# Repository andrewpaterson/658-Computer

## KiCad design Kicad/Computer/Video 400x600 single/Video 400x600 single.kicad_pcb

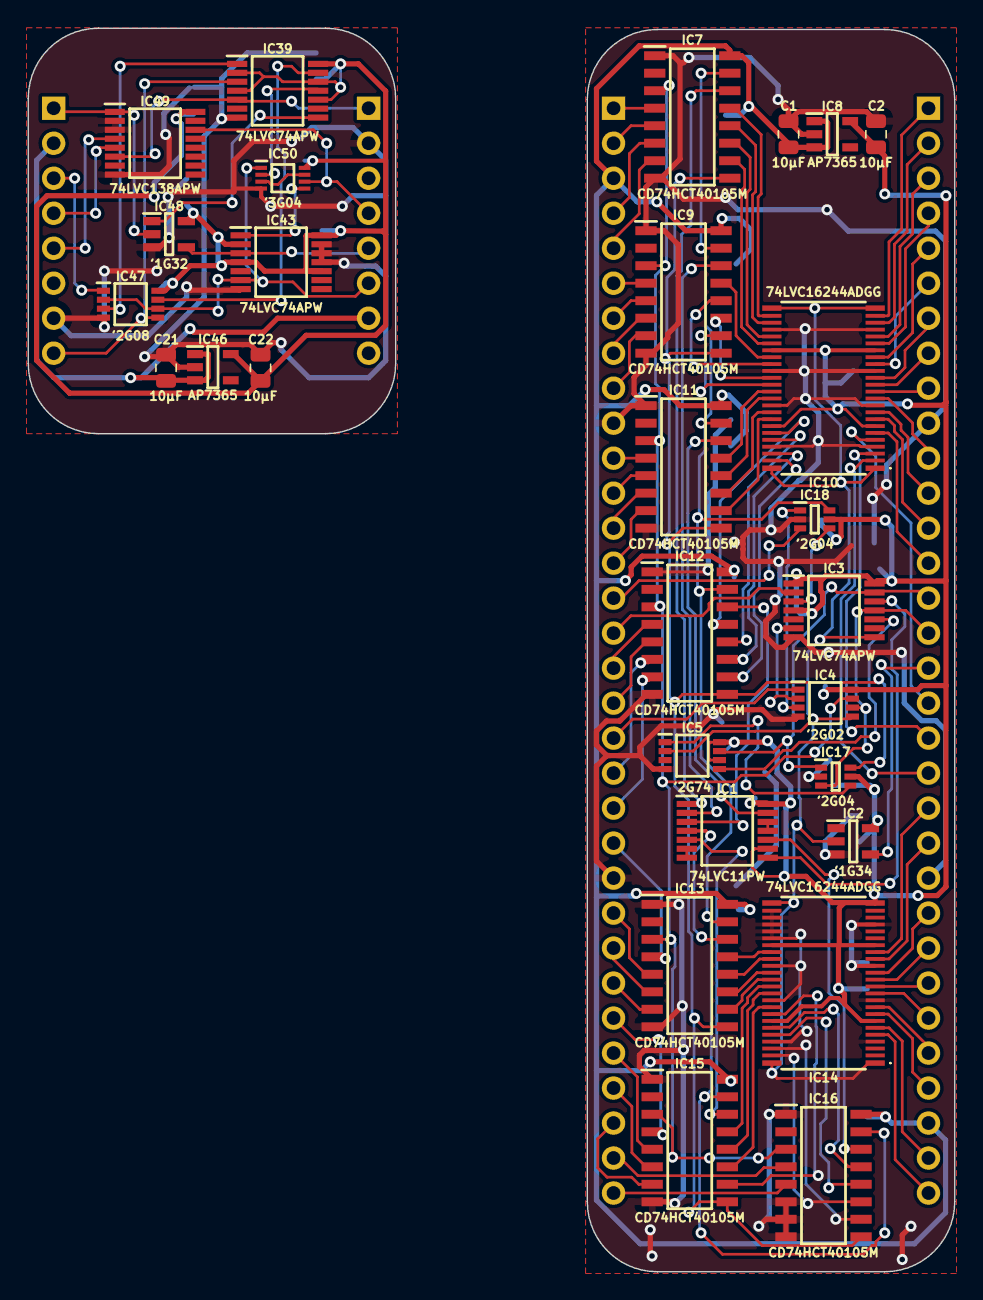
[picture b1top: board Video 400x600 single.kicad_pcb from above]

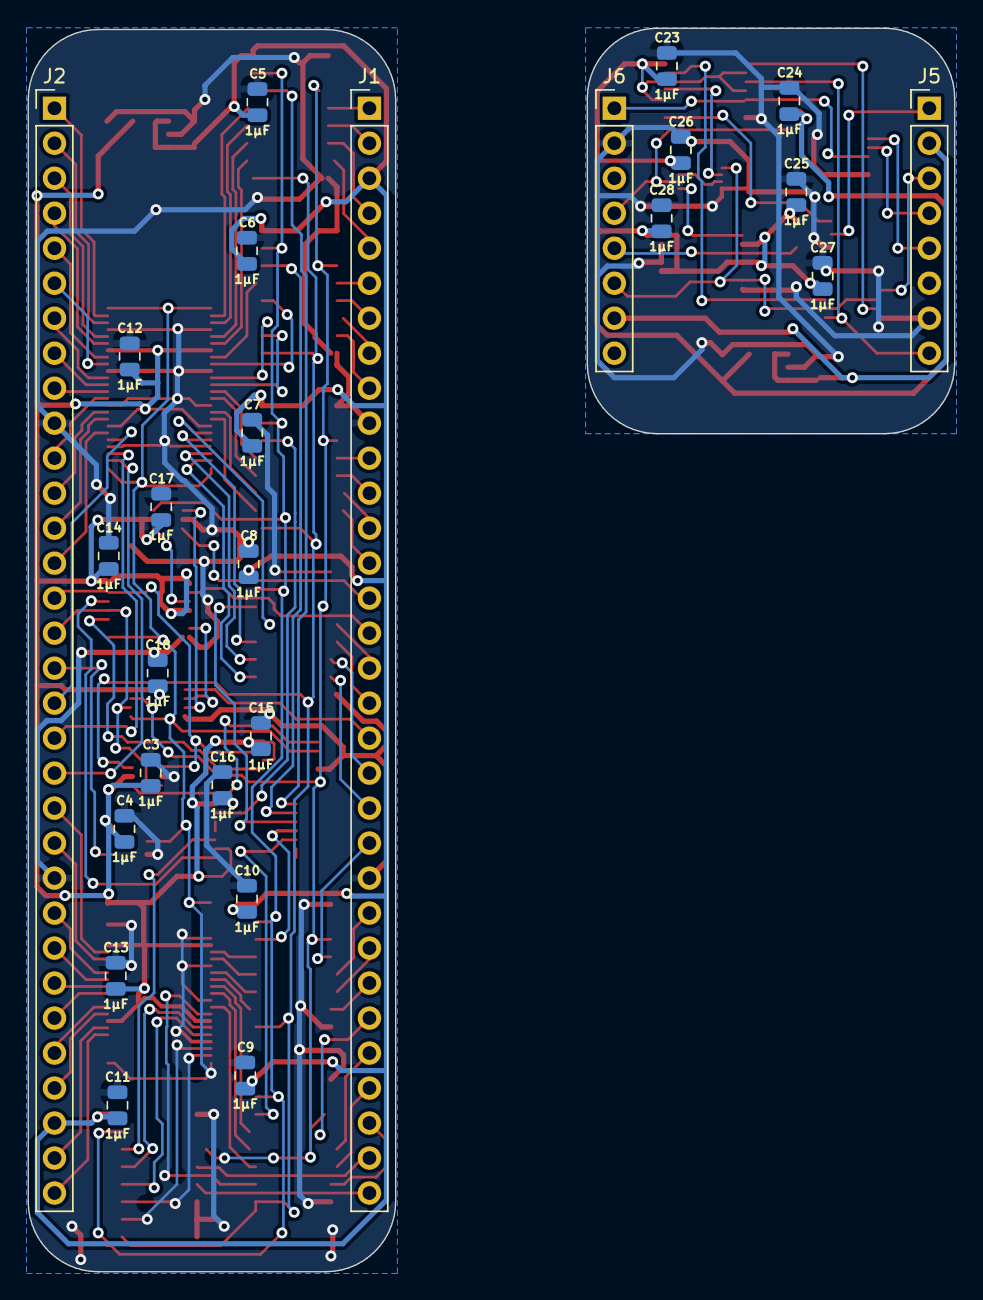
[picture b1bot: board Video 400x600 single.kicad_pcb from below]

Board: 2 copper layers, 67.2 x 90.3 mm, 54 parts (26 on the bottom side), 126 nets.

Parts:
C1, C2, C21, C22: 10µF; C_0805
C3, C4, C5, C6, C7, C8, C9, C10, C11, C12, C13, C14, C15, C16, C17, C18, C23, C24, C25, C26, C27, C28: 1μF; C_0805
IC1: 74LVC11PW,112; SOP65P640X110-14N
IC2: 74LVC1G34GV,125; SOT95P275X110-5N
IC3, IC39, IC43: 74LVC74APW,118; SOP65P640X110-14N
IC4: 74LVC2G02DP,125; SOP65P400X110-8N
IC5: 74LVC2G74DP,125; SOP65P400X110-8N
IC7, IC9, IC11, IC12, IC13, IC15, IC16: CD74HCT40105M; SOIC127P600X175-16N
IC8, IC46: AP7365-33WG-7; SOT95P285X130-5N
IC10, IC14: 74LVC16244ADGG,112; 74LVC16244ADGG112
IC17, IC18: 74LVC2G04GW-Q100H; SOP65P210X110-6N
IC47: 74LVC2G08DP-Q100H; SOP65P400X110-8N
IC48: 74LVC1G32GV,125; SOT95P275X110-5N
IC49: 74LVC138APW-Q100J; SOP65P640X110-16N
IC50: SN74LVC3G04DCUR; SOP50P310X90-8N
J1, J2: Conn_01x32_Pin; PinHeader_1x32_P2.54mm_Vertical
J5, J6: Conn_01x08_Pin; PinHeader_1x08_P2.54mm_Vertical

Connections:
/Asynchronous Write (FIFO)/3.3V: C2.1, C3.1, C4.1, C12.1, C13.1, C14.1, C15.1, C16.1, C17.1, C18.1, IC1.9 (3A), IC1.14 (3V), IC2.5 (3V), IC3.1 (~1RD), IC3.4 (~1SD), IC3.14 (3V), IC4.8 (3V), IC5.6 (~RD), IC5.8 (3V), IC8.5 (VOUT), IC10.7 (3V), IC10.18 (3V), IC10.31 (3V), IC10.42 (3V), IC14.7 (3V), IC14.18 (3V), IC14.24 (4~OE), IC14.31 (3V), IC14.42 (3V), IC17.5 (3V), IC18.5 (3V)
/Asynchronous Write (FIFO)/5V: C1.1, C5.1, C6.1, C7.1, C8.1, C9.1, C10.1, C11.1, IC7.16 (5V), IC8.1 (VIN), IC8.3 (EN), IC9.16 (5V), IC11.16 (5V), IC12.16 (5V), IC13.16 (5V), IC15.16 (5V), IC16.16 (5V), J1.3, J2.30
/Asynchronous Write (FIFO)/A0: IC11.4 (D0), J1.11
/Asynchronous Write (FIFO)/A1: IC11.5 (D1), J1.12
/Asynchronous Write (FIFO)/A2: IC11.6 (D2), J1.13
/Asynchronous Write (FIFO)/A3: IC11.7 (D3), J1.14
/Asynchronous Write (FIFO)/A4: IC12.4 (D0), J1.17
/Asynchronous Write (FIFO)/A5: IC12.5 (D1), J1.18
/Asynchronous Write (FIFO)/A6: IC12.6 (D2), J1.20
/Asynchronous Write (FIFO)/A7: IC12.7 (D3), J1.21
/Asynchronous Write (FIFO)/A8: IC13.4 (D0), J1.22
/Asynchronous Write (FIFO)/A9: IC13.5 (D1), J1.24
/Asynchronous Write (FIFO)/A10: IC13.6 (D2), J1.25
/Asynchronous Write (FIFO)/A11: IC13.7 (D3), J1.26
/Asynchronous Write (FIFO)/A12: IC15.4 (D0), J1.27
/Asynchronous Write (FIFO)/A13: IC15.5 (D1), J1.28
/Asynchronous Write (FIFO)/A14: IC15.6 (D2), J1.29
/Asynchronous Write (FIFO)/A15: IC15.7 (D3), J1.30
/Asynchronous Write (FIFO)/A16: IC16.4 (D0), J1.31
/Asynchronous Write (FIFO)/A17: IC16.5 (D1), J1.32
/Asynchronous Write (FIFO)/A_{OUT}0: IC10.37 (2A3), IC11.13 (Q0)
/Asynchronous Write (FIFO)/A_{OUT}1: IC10.38 (2A2), IC11.12 (Q1)
/Asynchronous Write (FIFO)/A_{OUT}2: IC10.40 (2A1), IC11.11 (Q2)
/Asynchronous Write (FIFO)/A_{OUT}3: IC10.41 (2A0), IC11.10 (Q3)
/Asynchronous Write (FIFO)/A_{OUT}4: IC10.43 (1A3), IC12.13 (Q0)
/Asynchronous Write (FIFO)/A_{OUT}5: IC10.44 (1A2), IC12.12 (Q1)
/Asynchronous Write (FIFO)/A_{OUT}6: IC10.46 (1A1), IC12.11 (Q2)
/Asynchronous Write (FIFO)/A_{OUT}7: IC10.47 (1A0), IC12.10 (Q3)
/Asynchronous Write (FIFO)/A_{OUT}8: IC13.13 (Q0), IC14.32 (3A3)
/Asynchronous Write (FIFO)/A_{OUT}9: IC13.12 (Q1), IC14.33 (3A2)
/Asynchronous Write (FIFO)/A_{OUT}10: IC13.11 (Q2), IC14.35 (3A1)
/Asynchronous Write (FIFO)/A_{OUT}11: IC13.10 (Q3), IC14.36 (3A0)
/Asynchronous Write (FIFO)/A_{OUT}12: IC14.37 (2A3), IC15.13 (Q0)
/Asynchronous Write (FIFO)/A_{OUT}13: IC14.38 (2A2), IC15.12 (Q1)
/Asynchronous Write (FIFO)/A_{OUT}14: IC14.40 (2A1), IC15.11 (Q2)
/Asynchronous Write (FIFO)/A_{OUT}15: IC14.41 (2A0), IC15.10 (Q3)
/Asynchronous Write (FIFO)/A_{OUT}16: IC14.43 (1A3), IC16.13 (Q0)
/Asynchronous Write (FIFO)/A_{OUT}17: IC14.44 (1A2), IC16.12 (Q1)
/Asynchronous Write (FIFO)/A_{OUT}18: IC14.47 (1A0), IC16.11 (Q2)
/Asynchronous Write (FIFO)/A_{OUT}19: IC14.46 (1A1), IC16.10 (Q3)
/Asynchronous Write (FIFO)/A_{W}0: IC10.12 (2Y3), J2.9
/Asynchronous Write (FIFO)/A_{W}1: IC10.11 (2Y2), J2.11
/Asynchronous Write (FIFO)/A_{W}2: IC10.9 (2Y1), J2.12
/Asynchronous Write (FIFO)/A_{W}3: IC10.8 (2Y0), J2.13
/Asynchronous Write (FIFO)/A_{W}4: IC10.6 (1Y3), J2.14
/Asynchronous Write (FIFO)/A_{W}5: IC10.5 (1Y2), J2.18
/Asynchronous Write (FIFO)/A_{W}6: IC10.3 (1Y1), J2.19
/Asynchronous Write (FIFO)/A_{W}7: IC10.2 (1Y0), J2.20
/Asynchronous Write (FIFO)/A_{W}8: IC14.17 (3Y3), J2.21
/Asynchronous Write (FIFO)/A_{W}9: IC14.16 (3Y2), J2.22
/Asynchronous Write (FIFO)/A_{W}10: IC14.14 (3Y1), J2.24
/Asynchronous Write (FIFO)/A_{W}11: IC14.13 (3Y0), J2.25
/Asynchronous Write (FIFO)/A_{W}12: IC14.12 (2Y3), J2.26
/Asynchronous Write (FIFO)/A_{W}13: IC14.11 (2Y2), J2.27
/Asynchronous Write (FIFO)/A_{W}14: IC14.9 (2Y1), J2.28
/Asynchronous Write (FIFO)/A_{W}15: IC14.8 (2Y0), J2.29
/Asynchronous Write (FIFO)/A_{W}16: IC14.6 (1Y3), J2.31
/Asynchronous Write (FIFO)/A_{W}17: IC14.5 (1Y2), J2.32
/Asynchronous Write (FIFO)/D0: IC7.4 (D0), J1.1
/Asynchronous Write (FIFO)/D1: IC7.5 (D1), J1.2
/Asynchronous Write (FIFO)/D2: IC7.6 (D2), J1.4
/Asynchronous Write (FIFO)/D3: IC7.7 (D3), J1.5
/Asynchronous Write (FIFO)/D4: IC9.4 (D0), J1.6
/Asynchronous Write (FIFO)/D5: IC9.5 (D1), J1.7
/Asynchronous Write (FIFO)/D6: IC9.6 (D2), J1.8
/Asynchronous Write (FIFO)/D7: IC9.7 (D3), J1.9
/Asynchronous Write (FIFO)/DOR0: IC1.1 (1A), IC7.14 (DOR)
/Asynchronous Write (FIFO)/DOR0·DOR1·DOR2: IC1.11 (3C), IC1.12 (1Y)
/Asynchronous Write (FIFO)/DOR1: IC1.2 (1B), IC9.14 (DOR)
/Asynchronous Write (FIFO)/DOR2: IC1.13 (1C), IC11.14 (DOR)
/Asynchronous Write (FIFO)/DOR3: IC1.3 (2A), IC12.14 (DOR)
/Asynchronous Write (FIFO)/DOR3·DOR4·DOR5: IC1.6 (2Y), IC1.7 (GND)
/Asynchronous Write (FIFO)/DOR4: IC1.4 (2B), IC13.14 (DOR)
/Asynchronous Write (FIFO)/DOR5: IC1.5 (2C), IC15.14 (DOR)
/Asynchronous Write (FIFO)/DOR6: IC1.10 (3B), IC16.14 (DOR)
/Asynchronous Write (FIFO)/D_{OUT}0: IC7.13 (Q0), IC10.26 (4A3)
/Asynchronous Write (FIFO)/D_{OUT}1: IC7.12 (Q1), IC10.27 (4A2)
/Asynchronous Write (FIFO)/D_{OUT}2: IC7.11 (Q2), IC10.29 (4A1)
/Asynchronous Write (FIFO)/D_{OUT}3: IC7.10 (Q3), IC10.30 (4A0)
/Asynchronous Write (FIFO)/D_{OUT}4: IC9.13 (Q0), IC10.32 (3A3)
/Asynchronous Write (FIFO)/D_{OUT}5: IC9.12 (Q1), IC10.33 (3A2)
/Asynchronous Write (FIFO)/D_{OUT}6: IC9.11 (Q2), IC10.35 (3A1)
/Asynchronous Write (FIFO)/D_{OUT}7: IC9.10 (Q3), IC10.36 (3A0)
/Asynchronous Write (FIFO)/D_{W}0: IC10.23 (4Y3), J2.1
/Asynchronous Write (FIFO)/D_{W}1: IC10.22 (4Y2), J2.2
/Asynchronous Write (FIFO)/D_{W}2: IC10.20 (4Y1), J2.3
/Asynchronous Write (FIFO)/D_{W}3: IC10.19 (4Y0), J2.4
/Asynchronous Write (FIFO)/D_{W}4: IC10.17 (3Y3), J2.5
/Asynchronous Write (FIFO)/D_{W}5: IC10.16 (3Y2), J2.6
/Asynchronous Write (FIFO)/D_{W}6: IC10.14 (3Y1), J2.7
/Asynchronous Write (FIFO)/D_{W}7: IC10.13 (3Y0), J2.8
/Asynchronous Write (FIFO)/Data Ready: IC1.8 (3Y), IC3.12 (2D)
/Asynchronous Write (FIFO)/Data Write Done: IC4.3 (2Y), IC18.1 (1A)
/Asynchronous Write (FIFO)/GND: C1.2, C2.2, C3.2, C4.2, C5.2, C6.2, C7.2, C8.2, C9.2, C10.2, C11.2, C12.2, C13.2, C14.2, C15.2, C16.2, C17.2, C18.2, IC2.3 (GND), IC3.7 (GND), IC4.4 (GND), IC5.4 (GND), IC7.1 (~EN(TSC)), IC7.8 (GND), IC8.2 (GND), IC9.1 (~EN(TSC)), IC9.8 (GND), IC10.4 (GND), IC10.10 (GND), IC10.15 (GND), IC10.21 (GND), IC10.28 (GND), IC10.34 (GND), IC10.39 (GND), IC10.45 (GND), IC11.1 (~EN(TSC)), IC11.8 (GND), IC12.1 (~EN(TSC)), IC12.8 (GND), IC13.1 (~EN(TSC)), IC13.8 (GND), IC14.4 (GND), IC14.10 (GND), IC14.15 (GND), IC14.21 (GND), IC14.26 (4A3), IC14.27 (4A2), IC14.28 (GND), IC14.29 (4A1), IC14.30 (4A0), IC14.34 (GND), IC14.39 (GND), IC14.45 (GND), IC15.1 (~EN(TSC)), IC15.8 (GND), IC16.1 (~EN(TSC)), IC16.6 (D2), IC16.7 (D3), IC16.8 (GND), IC17.2 (GND), IC18.2 (GND), J1.10, J1.23, J2.10, J2.23
/Asynchronous Write (FIFO)/PHI2: IC3.2 (1D), J1.16
/Asynchronous Write (FIFO)/Pixel Clock: IC3.11 (2CP), IC4.6 (2B), IC17.3 (2A), J2.16
/Asynchronous Write (FIFO)/RESET: IC7.9 (MR), IC9.9 (MR), IC11.9 (MR), IC12.9 (MR), IC13.9 (MR), IC15.9 (MR), IC16.9 (MR), IC17.6 (1Y)
/Asynchronous Write (FIFO)/SI: IC4.7 (1Y), IC7.3 (SI), IC9.3 (SI), IC11.3 (SI), IC12.3 (SI), IC13.3 (SI), IC15.3 (SI), IC16.3 (SI)
/Asynchronous Write (FIFO)/Source Clock: IC18.3 (2A), J1.15
/Asynchronous Write (FIFO)/~CS: IC4.1 (1A), J1.19
/Asynchronous Write (FIFO)/~Clear Data Write: IC3.10 (~2SD), IC5.5 (Q)
/Asynchronous Write (FIFO)/~Data Write Done: IC7.15 (~SO), IC9.15 (~SO), IC11.15 (~SO), IC12.15 (~SO), IC13.15 (~SO), IC15.15 (~SO), IC16.15 (~SO), IC18.6 (1Y)
/Asynchronous Write (FIFO)/~Data Write: IC2.2 (A), IC3.8 (~2Q), IC4.5 (2A), IC5.2 (D), IC10.1 (1~OE), IC10.24 (4~OE), IC10.25 (3~OE), IC10.48 (2~OE), IC14.1 (1~OE), IC14.25 (3~OE), IC14.48 (2~OE)
/Asynchronous Write (FIFO)/~Data Write_{OUT}: IC2.4 (Y), J2.17
/Asynchronous Write (FIFO)/~Pixel Clock: IC5.1 (CP), IC17.4 (2Y)
/Asynchronous Write (FIFO)/~RESET: IC3.13 (~2RD), IC5.7 (~SD), IC17.1 (1A), J2.15
/Asynchronous Write (FIFO)/~Source Clock: IC3.3 (1CP), IC18.4 (2Y)
/Asynchronous Write (FIFO)/~Video SI: IC3.6 (~1Q), IC4.2 (1B)
/Asynchronous Write (PHI2 Hold)/3.3V: C22.1, C23.1, C24.1, C25.1, C26.1, C27.1, C28.1, IC39.2 (1D), IC39.4 (~1SD), IC39.10 (~2SD), IC39.12 (2D), IC39.14 (3V), IC43.2 (1D), IC43.4 (~1SD), IC43.10 (~2SD), IC43.14 (3V), IC46.5 (VOUT), IC47.8 (3V), IC48.5 (3V), IC49.16 (3V), IC50.8 (3V)
/Asynchronous Write (PHI2 Hold)/5V: C21.1, IC46.1 (VIN), IC46.3 (EN), J5.2, J6.7
/Asynchronous Write (PHI2 Hold)/GND: C21.2, C22.2, C23.2, C24.2, C25.2, C26.2, C27.2, C28.2, IC39.7 (GND), IC43.7 (GND), IC43.11 (2CP), IC43.12 (2D), IC43.13 (~2RD), IC46.2 (GND), IC47.4 (GND), IC48.3 (GND), IC49.2 (A1), IC49.3 (A2), IC49.8 (GND), IC50.4 (GND), J5.7, J6.2
/Asynchronous Write (PHI2 Hold)/PHI2: IC39.3 (1CP), IC47.5 (2A), J5.8
/Asynchronous Write (PHI2 Hold)/PHI2 Risen: IC39.5 (1Q), IC49.6 (E3), J6.1
/Asynchronous Write (PHI2 Hold)/Pixel Clock: IC48.2 (A), IC49.1 (A0), J5.1
/Asynchronous Write (PHI2 Hold)/Video Write Waiting: IC39.11 (2CP), IC50.2 (3Y)
/Asynchronous Write (PHI2 Hold)/~CS: IC49.4 (~E1), J5.5
/Asynchronous Write (PHI2 Hold)/~RESET: IC47.1 (1A), J5.3
/Asynchronous Write (PHI2 Hold)/~Video Write Done: IC43.6 (~1Q), IC47.2 (1B), IC47.6 (2B), IC50.1 (1A), J6.6
/Asynchronous Write (PHI2 Hold)/~Video Write Progress: IC39.8 (~2Q), IC48.1 (B)
/Asynchronous Write (PHI2 Hold)/~Video Write Waiting: IC49.14 (~Y1), IC50.6 (3A), J6.4
/Asynchronous Write (PHI2 Hold)/~Video Write: IC43.3 (1CP), IC48.4 (Y), J6.5
/Asynchronous Write (PHI2 Hold)/~WD: IC49.5 (~E2), J5.4
unnamed: IC39.1 (~1RD), IC47.3 (2Y)
unnamed: IC39.13 (~2RD), IC47.7 (1Y)
unnamed: IC43.1 (~1RD), IC50.5 (2Y)
unnamed: IC50.3 (2A), IC50.7 (1Y)
